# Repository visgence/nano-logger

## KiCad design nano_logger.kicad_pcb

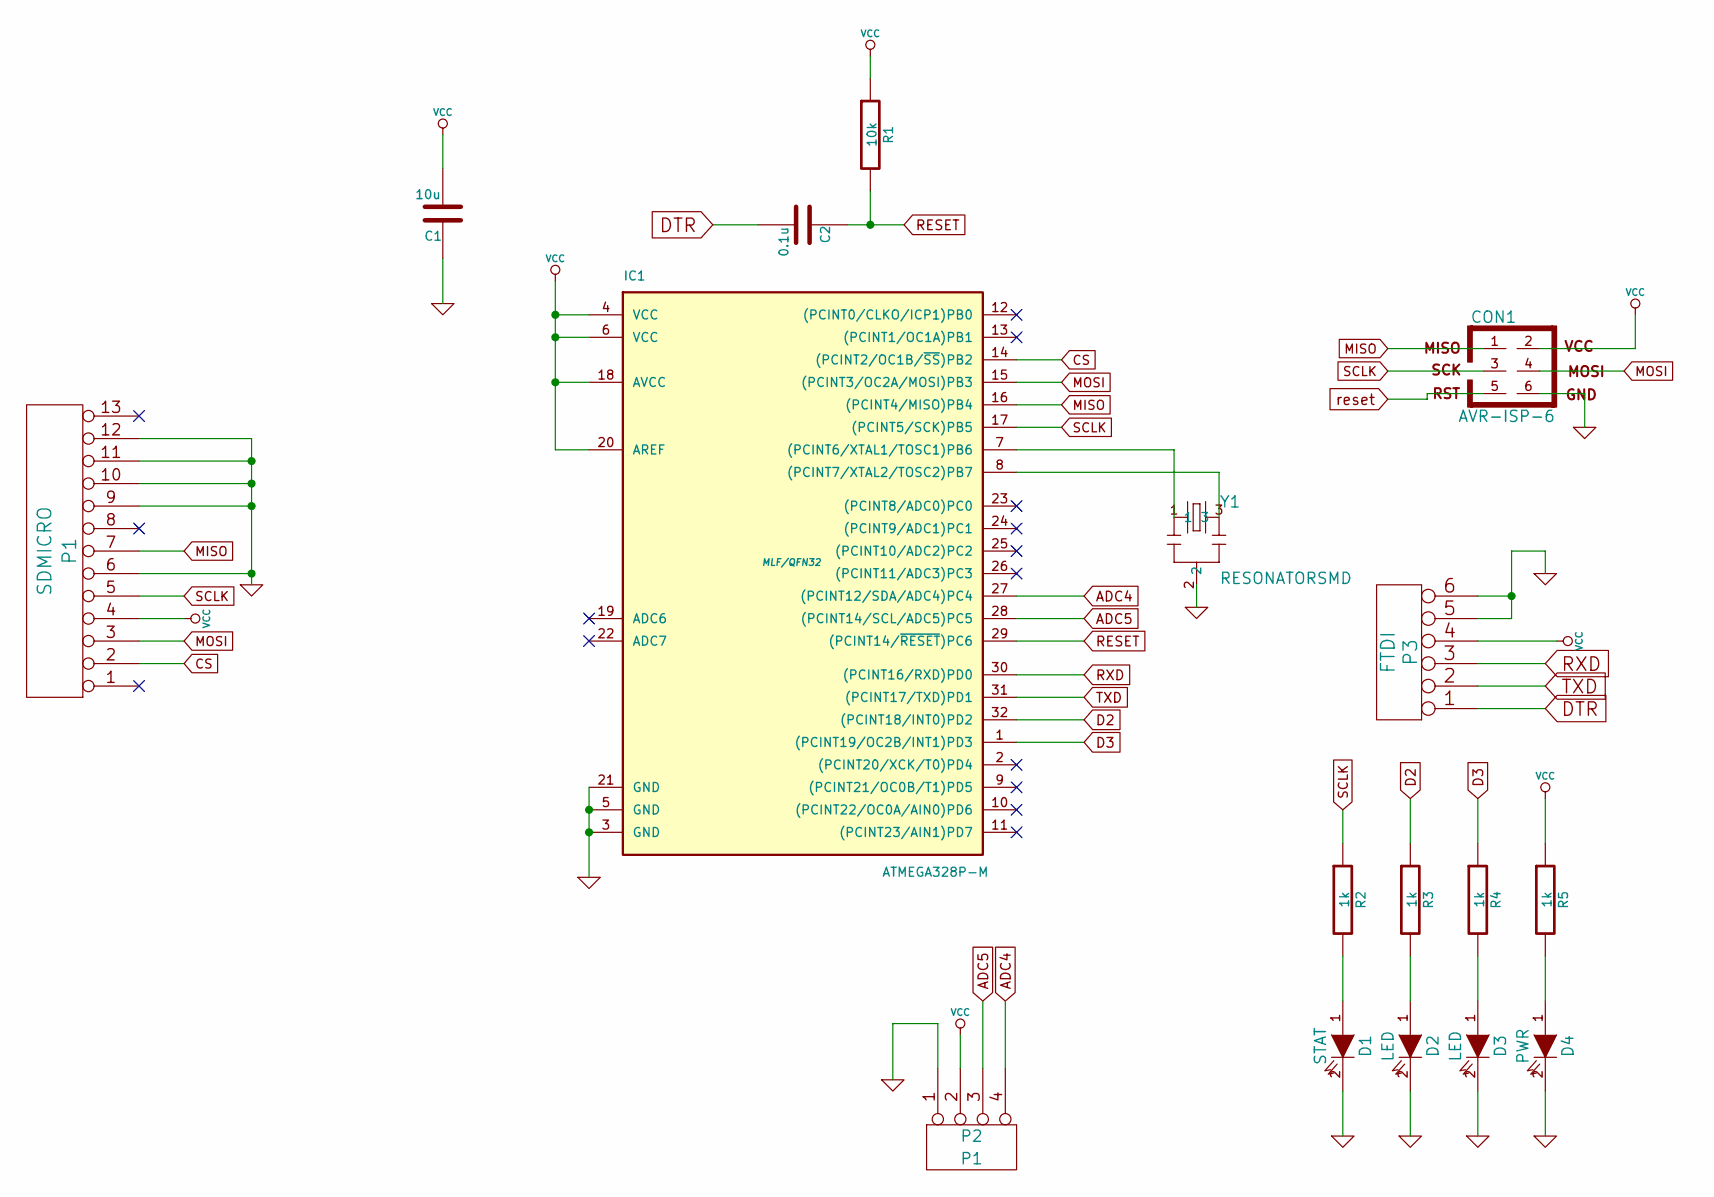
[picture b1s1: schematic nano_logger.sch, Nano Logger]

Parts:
C1: 10u
C2: 0.1u
CON1: AVR-ISP-6
D1: STAT
D2, D3: LED
D4: PWR
IC1: ATMEGA328P-M; MLF/QFN32
P1: SDMICRO
P2: P1
P3: FTDI
R1: 10k
R2, R3, R4, R5: 1k
Y1: RESONATORSMD

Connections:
ADC4: IC1.27 ((PCINT12/SDA/ADC4)PC4), P2.4
ADC5: IC1.28 ((PCINT14/SCL/ADC5)PC5), P2.3
CS: IC1.14 ((PCINT2/OC1B/~SS~)PB2), P1.2
D2: IC1.32 ((PCINT18/INT0)PD2), R3.1
D3: IC1.1 ((PCINT19/OC2B/INT1)PD3), R4.1
DTR: C2.2, P3.1
GND: C1.1, CON1.6, D1.2 (K), D2.2 (K), D3.2 (K), D4.2 (K), IC1.3 (GND), IC1.5 (GND), IC1.21 (GND), P1.6, P1.9, P1.10, P1.11, P1.12, P2.1, P3.5, P3.6, Y1.2
MISO: CON1.1, IC1.16 ((PCINT4/MISO)PB4), P1.7
MOSI: CON1.4, IC1.15 ((PCINT3/OC2A/MOSI)PB3), P1.3
unnamed: D1.1 (A), R2.2
unnamed: D2.1 (A), R3.2
unnamed: D3.1 (A), R4.2
unnamed: D4.1 (A), R5.2
unnamed: IC1.7 ((PCINT6/XTAL1/TOSC1)PB6), Y1.1
unnamed: IC1.8 ((PCINT7/XTAL2/TOSC2)PB7), Y1.3
RESET: C2.1, CON1.5, IC1.29 ((PCINT14/~RESET~)PC6), R1.2
RXD: IC1.30 ((PCINT16/RXD)PD0), P3.3
SCLK: CON1.3, IC1.17 ((PCINT5/SCK)PB5), P1.5, R2.1
TXD: IC1.31 ((PCINT17/TXD)PD1), P3.2
VCC: C1.2, CON1.2, IC1.4 (VCC), IC1.6 (VCC), IC1.18 (AVCC), IC1.20 (AREF), P1.4, P2.2, P3.4, R1.1, R5.1

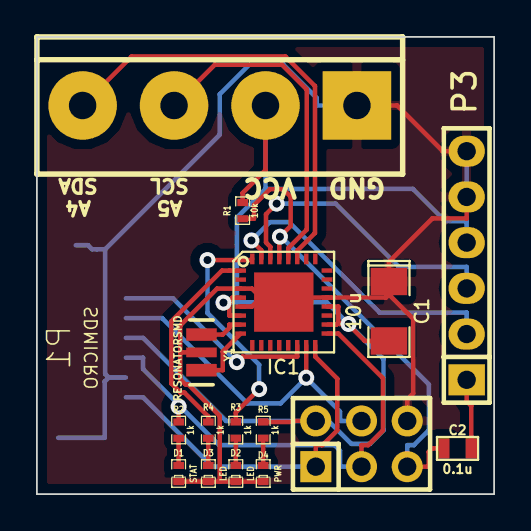
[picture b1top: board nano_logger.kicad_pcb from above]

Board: 2 copper layers, 25.4 x 25.4 mm, 17 parts (1 on the bottom side), 20 nets.

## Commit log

2014-05-07 Fixed atmega footprint
2014-05-11 Moved parts around and routed
2014-06-07 Updated nano_logger to use relative path for visgence parts library
2014-06-07 Updated libraries for nano_logger.pro
